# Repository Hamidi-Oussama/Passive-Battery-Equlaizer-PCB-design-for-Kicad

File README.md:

# Passive-Battery-Equlaizer-PCB-design-for-Kicad
This is a project where i designed a PCB for Passive Battery Equlaizer circuit using kicad 8.0

PROJECT_FILE contains the kicad project files, you can check it out and give me any ideas to improve 😊
Project name:  PCB design for Passive Battery Equlaizer

NOTE: the TXT file for fastcad simulation if needed, "https://falstad.com/circuit/"

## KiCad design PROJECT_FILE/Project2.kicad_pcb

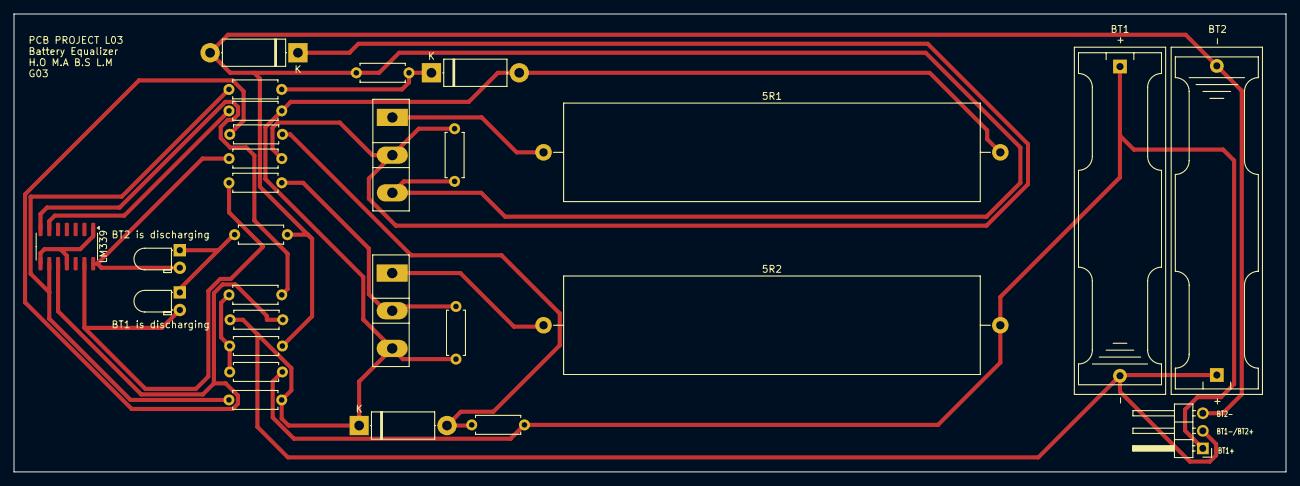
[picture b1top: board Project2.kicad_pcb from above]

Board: 2 copper layers, 183.9 x 66.2 mm, 28 parts (0 on the bottom side), 18 nets.

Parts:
5R1, 5R2: 50W; R_Axial_Power_L60.0mm_W14.0mm_P66.04mm
BT1, BT2: Battery_Cell; BatteryHolder_Keystone_2466_1xAAA
BT1 is discharging, BT2 is discharging: LED; LED_D3.0mm_Horizontal_O1.27mm_Z2.0mm
D1: D_Schottky; D_5W_P12.70mm_Horizontal
D2, D3: D; D_5W_P12.70mm_Horizontal
J1: Conn_01x03_Pin; PinHeader_1x03_P2.54mm_Horizontal
LM339: SOIC-14_3.9x8.7mm_P1.27mm
Q1, Q2: NMOS; TO-247-3_Vertical
R1, R2: 20k; R_Axial_DIN0207_L6.3mm_D2.5mm_P7.62mm_Horizontal
R3, R6, R13, R14, R15: 10k; R_Axial_DIN0207_L6.3mm_D2.5mm_P7.62mm_Horizontal
R4, R5: 1M; R_Axial_DIN0207_L6.3mm_D2.5mm_P7.62mm_Horizontal
R7, R12: 31k; R_Axial_DIN0207_L6.3mm_D2.5mm_P7.62mm_Horizontal
R8, R11: 51; R_Axial_DIN0207_L6.3mm_D2.5mm_P7.62mm_Horizontal
R9, R10: 100k; R_Axial_DIN0207_L6.3mm_D2.5mm_P7.62mm_Horizontal

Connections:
GND: BT2.2 (-), D1.2 (A), J1.3, Q1.3 (S), R2.1, R3.2, R5.1, R10.1
unnamed: 5R2.2, BT1.1 (+), J1.1, R1.2, R9.2
unnamed: 5R1.2, BT1.2 (-), BT2.1 (+), D2.1 (K), D3.2 (A), J1.2, Q2.3 (S), R4.1, R8.2, R11.1, R14.2
unnamed: D1.1 (K), Q1.2 (G), R5.2, R15.2
unnamed: D2.2 (A), R7.2, R9.1
unnamed: D3.1 (K), R10.2, R12.1
unnamed: BT2 is discharging.2 (A), LM339.14, R15.1
unnamed: BT1 is discharging.1 (K), BT2 is discharging.1 (K), R3.1
unnamed: BT1 is discharging.2 (A), LM339.13, R6.1
unnamed: LM339.1, LM339.8, LM339.11
unnamed: 5R1.1, Q1.1 (D)
unnamed: 5R2.1, Q2.1 (D)
unnamed: Q2.2 (G), R4.2, R6.2
unnamed: R1.1, R2.2, R13.2
unnamed: LM339.10, R7.1, R11.2
unnamed: LM339.7, R13.1
unnamed: LM339.6, R14.1
unnamed: LM339.9, R8.1, R12.2
